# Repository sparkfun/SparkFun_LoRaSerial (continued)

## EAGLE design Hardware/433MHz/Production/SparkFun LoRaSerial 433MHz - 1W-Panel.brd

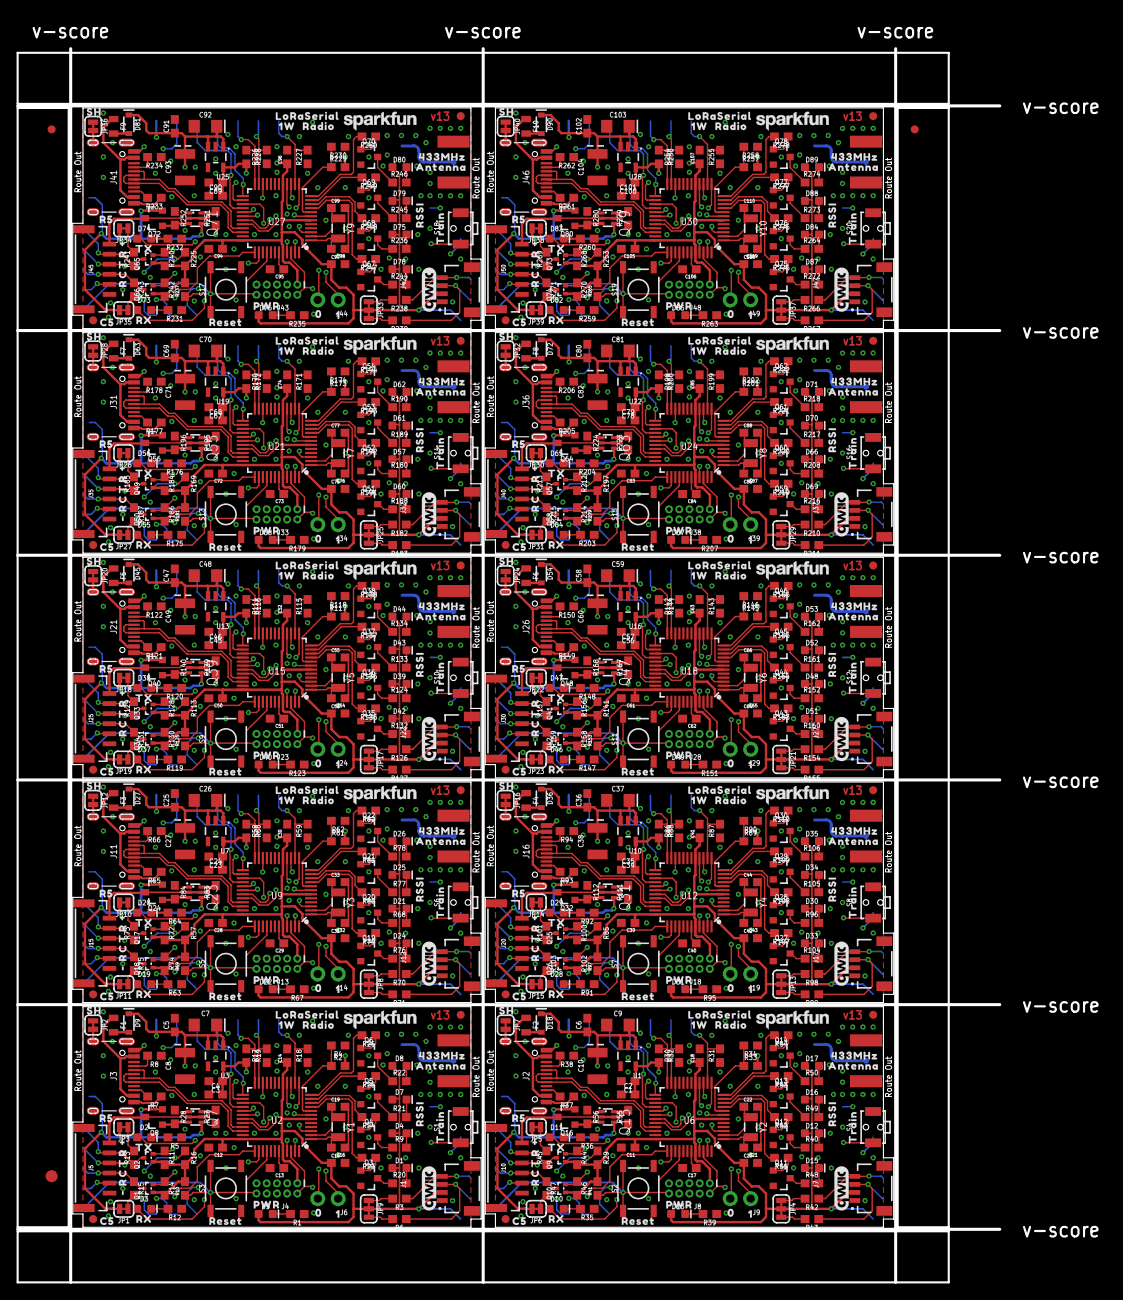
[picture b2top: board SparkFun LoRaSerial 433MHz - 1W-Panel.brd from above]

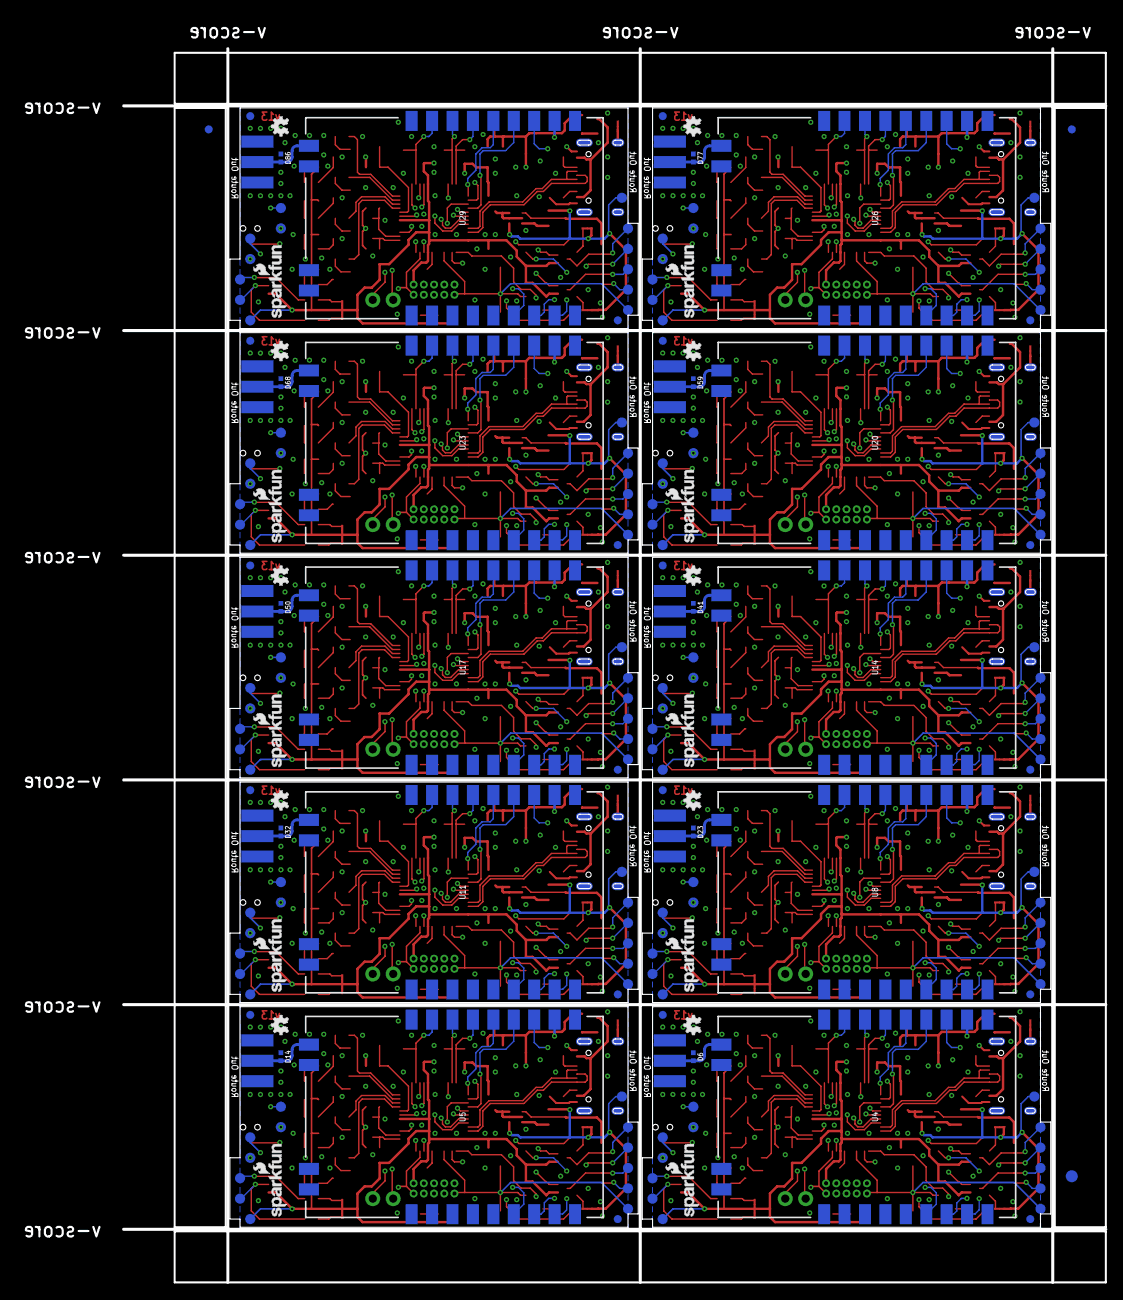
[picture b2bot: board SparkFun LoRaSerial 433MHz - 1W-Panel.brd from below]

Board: 4 copper layers, 122.2 x 153.5 mm, 1166 parts (203 on the bottom side), 660 nets.

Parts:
C1, C3, C5, C6, C23, C25, C34, C36, C45, C47, C56, C58, C67, C69, C78, C80, C89, C91, C100, C102: 1.0uF; 0603
C2, C4, C11, C12, C13, C14, C15, C17, C18, C20, C24, C28, C29, C30, C31, C35, C39, C40, C41, C42, C46, C50, C51, C52, C53, C57, C61, C62, C63, C64, C68, C72, C73, C74, C75, C79, C83, C84, C85, C86, C90, C94, C95, C96, C97, C101, C105, C106, C107, C108: 0.1uF; 0603
C7, C9, C26, C37, C48, C59, C70, C81, C92, C103: 10uF; EIA3216
C8, C10, C27, C38, C49, C60, C71, C82, C93, C104: 47uF; EIA3528
C16, C19, C21, C22, C32, C33, C43, C44, C54, C55, C65, C66, C76, C77, C87, C88, C98, C99, C109, C110: 15pF; 0603
D1, D4, D7, D8, D12, D15, D16, D17, D21, D24, D25, D26, D30, D33, D34, D35, D39, D42, D43, D44, D48, D51, D52, D53, D57, D60, D61, D62, D66, D69, D70, D71, D75, D78, D79, D80, D84, D87, D88, D89: GREEN; LED-0603
D2, D11, D20, D29, D38, D47, D56, D65, D74, D83: BLUE; LED-0603
D3, D10, D19, D28, D37, D46, D55, D64, D73, D82: Yellow; LED-0603
D5, D13, D22, D31, D40, D49, D58, D67, D76, D85: RED; LED-0603
D6, D14, D23, D32, D41, D50, D59, D68, D77, D86: PESD0402; 0402-TIGHT
D9, D18, D27, D36, D45, D54, D63, D72, D81, D90: 3A/10V/280mV; SOD-323
E1, E2, E3, E4, E5, E6, E7, E8, E9, E10: SMA; SMA-EDGE
E$1, E$2, E$3, E$4: FIDUCIAL-1X2
E$5, E$6: FIDUCIAL-1.5X3
F1, F2, F3, F4, F5, F6, F7, F8, F9, F10: 6V 0.5A; 0805
FID1, FID2, FID3, FID4, FID5, FID6, FID7, FID8, FID9, FID10, FID11, FID12, FID13, FID14, FID15, FID16, FID17, FID18, FID19, FID20, FID21, FID22, FID23, FID24, FID25, FID26, FID27, FID28, FID29, FID30, FID31, FID32, FID33, FID34, FID35, FID36, FID37, FID38, FID39, FID40: FIDUCIAL1X2; FIDUCIAL-1X2
J1, J7, J12, J17, J22, J27, J32, J37, J42, J47: QWIIC_RIGHT_ANGLE; JST04_1MM_RA
J2, J3, J11, J16, J21, J26, J31, J36, J41, J46: USB C; USB-C-16P
J4, J8, J13, J18, J23, J28, J33, J38, J43, J48: JTAG; 2X5-PTH-1.27MM-NO_SILK
J5, J10, J15, J20, J25, J30, J35, J40, J45, J50: JST-6-SMD-1.25MM-LOCKING
J6, J9, J14, J19, J24, J29, J34, J39, J44, J49: 1X02_NO_SILK
JP1, JP3, JP5, JP6, JP10, JP11, JP14, JP15, JP18, JP19, JP22, JP23, JP26, JP27, JP30, JP31, JP34, JP35, JP38, JP39: JUMPER-SMT_2_NC_TRACE_SILK; SMT-JUMPER_2_NC_TRACE_SILK
JP2, JP7, JP12, JP16, JP20, JP24, JP28, JP32, JP36, JP40: SMT-JUMPER_2_NC_TRACE_SILK
JP4, JP8, JP9, JP13, JP17, JP21, JP25, JP29, JP33, JP37: JUMPER-SMT_3_2-NC_TRACE_SILK; SMT-JUMPER_3_2-NC_TRACE_SILK
LOGO1, LOGO5, LOGO9, LOGO13, LOGO17, LOGO21, LOGO25, LOGO29, LOGO33, LOGO37: SFE_LOGO_NAME9_MM; SFE_LOGO_NAME_9MM
LOGO2, LOGO6, LOGO10, LOGO14, LOGO18, LOGO22, LOGO26, LOGO30, LOGO34, LOGO38: SFE_LOGO_NAME_FLAME9_MM; SFE_LOGO_NAME_FLAME_9MM
LOGO3, LOGO8, LOGO12, LOGO16, LOGO20, LOGO24, LOGO28, LOGO32, LOGO36, LOGO40: QWIIC_LOGO_CONNECTOR; QWIIC_5.5MM
LOGO4, LOGO7, LOGO11, LOGO15, LOGO19, LOGO23, LOGO27, LOGO31, LOGO35, LOGO39: OSHW-LOGOMINI; OSHW-LOGO-MINI
Q1, Q2, Q9, Q10, Q17, Q18, Q25, Q26, Q33, Q34, Q41, Q42, Q49, Q50, Q57, Q58, Q65, Q66, Q73, Q74: 20V/0.2A/8MHz/1.2Ω/1Vth; SOT-416FL
Q3, Q4, Q5, Q6, Q11, Q12, Q13, Q14, Q19, Q20, Q21, Q22, Q27, Q28, Q29, Q30, Q35, Q36, Q37, Q38, Q43, Q44, Q45, Q46, Q51, Q52, Q53, Q54, Q59, Q60, Q61, Q62, Q67, Q68, Q69, Q70, Q75, Q76, Q77, Q78: 600mA/40V; SOT23-3
Q7, Q15, Q23, Q31, Q39, Q47, Q55, Q63, Q71, Q79: SOT363_PHILIPS
Q8, Q16, Q24, Q32, Q40, Q48, Q56, Q64, Q72, Q80: 20V/4.2A/52mΩ/1.4W; SOT23-3
R1, R23, R24, R25, R26, R39, R51, R52, R53, R54, R67, R79, R80, R81, R82, R95, R107, R108, R109, R110, R123, R135, R136, R137, R138, R151, R163, R164, R165, R166, R179, R191, R192, R193, R194, R207, R219, R220, R221, R222, R235, R247, R248, R249, R250, R263, R275, R276, R277, R278: 1k; 0603
R2, R10, R33, R41, R61, R69, R89, R97, R117, R125, R145, R153, R173, R181, R201, R209, R229, R237, R257, R265: 10k; 0603
R3, R6, R11, R13, R14, R15, R42, R43, R44, R45, R46, R47, R70, R71, R72, R73, R74, R75, R98, R99, R100, R101, R102, R103, R126, R127, R128, R129, R130, R131, R154, R155, R156, R157, R158, R159, R182, R183, R184, R185, R186, R187, R210, R211, R212, R213, R214, R215, R238, R239, R240, R241, R242, R243, R266, R267, R268, R269, R270, R271: 2.2k; 0603
R4, R34, R62, R90, R118, R146, R174, R202, R230, R258: 20k; 0603
R5, R36, R64, R92, R120, R148, R176, R204, R232, R260: 0; 0603
R7, R8, R37, R38, R65, R66, R93, R94, R121, R122, R149, R150, R177, R178, R205, R206, R233, R234, R261, R262: 5.1k; 0603
R9, R20, R21, R22, R40, R48, R49, R50, R68, R76, R77, R78, R96, R104, R105, R106, R124, R132, R133, R134, R152, R160, R161, R162, R180, R188, R189, R190, R208, R216, R217, R218, R236, R244, R245, R246, R264, R272, R273, R274: 22Ω; 0603
R12, R35, R63, R91, R119, R147, R175, R203, R231, R259: 330; 0603
R16, R17, R18, R19, R27, R29, R30, R31, R32, R55, R57, R58, R59, R60, R83, R85, R86, R87, R88, R111, R113, R114, R115, R116, R139, R141, R142, R143, R144, R167, R169, R170, R171, R172, R195, R197, R198, R199, R200, R223, R225, R226, R227, R228, R251, R253, R254, R255, R256, R279: 100k; 0603
R28, R56, R84, R112, R140, R168, R196, R224, R252, R280: 1M; 0603
S1, S4, S6, S8, S10, S12, S14, S16, S18, S20: Train; TACTILE_SWITCH_SMD_RIGHT_ANGLE
S2, S3, S5, S7, S9, S11, S13, S15, S17, S19: Reset; TACTILE_SWITCH_SMD_5.2MM
TP1, TP2, TP3, TP4, TP5, TP6, TP7, TP8, TP9, TP10, TP11, TP12, TP13, TP14, TP15, TP16, TP17, TP18, TP19, TP20, TP21, TP22, TP23, TP24, TP25, TP26, TP27, TP28, TP29, TP30, TP31, TP32, TP33, TP34, TP35, TP36, TP37, TP38, TP39, TP40, TP41, TP42, TP43, TP44, TP45, TP46, TP47, TP48, TP49, TP50, TP51, TP52, TP53, TP54, TP55, TP56, TP57, TP58, TP59, TP60, TP61, TP62, TP63, TP64, TP65, TP66, TP67, TP68, TP69, TP70, TP71, TP72, TP73, TP74, TP75, TP76, TP77, TP78, TP79, TP80, TP81, TP82, TP83, TP84, TP85, TP86, TP87, TP88, TP89, TP90, TP91, TP92, TP93, TP94, TP95, TP96, TP97, TP98, TP99, TP100, TP101, TP102, TP103, TP104, TP105, TP106, TP107, TP108, TP109, TP110, TP111, TP112, TP113, TP114, TP115, TP116, TP117, TP118, TP119, TP120, TP121, TP122, TP123, TP124, TP125, TP126, TP127, TP128, TP129, TP130: PAD.03X.05
U1, U3, U7, U10, U13, U16, U19, U22, U25, U28: 3.3V/150mA; SOT23-5
U2, U6, U9, U12, U15, U18, U21, U24, U27, U30: ATSAMD21G-A; TQFP-48
U4, U5, U8, U11, U14, U17, U20, U23, U26, U29: E19-915M30S; E19-433M30S
U$1, U$35, U$57, U$79, U$101, U$123, U$145, U$167, U$189, U$211: 1W1
U$2, U$3, U$45, U$67, U$89, U$111, U$133, U$155, U$177, U$199: RESET0
U$4, U$36, U$58, U$80, U$102, U$124, U$146, U$168, U$190, U$212: TRAIN0
U$5, U$25, U$47, U$69, U$91, U$113, U$135, U$157, U$179, U$201: RADIO2
U$6, U$41, U$63, U$85, U$107, U$129, U$151, U$173, U$195, U$217: 01
U$7, U$40, U$62, U$84, U$106, U$128, U$150, U$172, U$194, U$216: PWR0
U$8, U$44, U$66, U$88, U$110, U$132, U$154, U$176, U$198, U$220: 433MHZ0
U$9, U$24, U$46, U$68, U$90, U$112, U$134, U$156, U$178, U$200: ANTENNA1
U$10, U$26, U$48, U$70, U$92, U$114, U$136, U$158, U$180, U$202: RX1
U$11, U$27, U$49, U$71, U$93, U$115, U$137, U$159, U$181, U$203: TX0
U$12, U$28, U$50, U$72, U$94, U$116, U$138, U$160, U$182, U$204: #0
U$13, U$29, U$51, U$73, U$95, U$117, U$139, U$161, U$183, U$205: #1
U$14, U$30, U$52, U$74, U$96, U$118, U$140, U$162, U$184, U$206: R3
U$15, U$31, U$53, U$75, U$97, U$119, U$141, U$163, U$185, U$207: T2
U$16, U$32, U$54, U$76, U$98, U$120, U$142, U$164, U$186, U$208: C0
U$17, U$33, U$55, U$77, U$99, U$121, U$143, U$165, U$187, U$209: R1
U$18, U$34, U$56, U$78, U$100, U$122, U$144, U$166, U$188, U$210: LORASERIAL0
U$19, U$37, U$59, U$81, U$103, U$125, U$147, U$169, U$191, U$213: C50
U$20, U$38, U$60, U$82, U$104, U$126, U$148, U$170, U$192, U$214: R50
U$21, U$39, U$61, U$83, U$105, U$127, U$149, U$171, U$193, U$215: RSSI0
U$22, U$42, U$64, U$86, U$108, U$130, U$152, U$174, U$196, U$218: 10
U$23, U$43, U$65, U$87, U$109, U$131, U$153, U$175, U$197, U$219: SH0
Y1, Y2, Y3, Y4, Y5, Y6, Y7, Y8, Y9, Y10: 32.768kHz; CRYSTAL-SMD-3.2X1.5MM

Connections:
3.3V: C3.1, C4.2, C12.1, C14.1, C15.1, D1.A, D4.A, D5.A, D7.A, D8.A, J1.2, J4.1, JP9.2, Q1.1, Q2.1, R2.2, R10.2, R11.2, R14.2, R16.2, R17.2, TP1.1, U2.6, U2.17, U2.36, U2.44, U3.5
3.3V1: C1.1, C2.2, C11.1, C18.1, C20.1, D12.A, D13.A, D15.A, D16.A, D17.A, J7.2, J8.1, JP4.2, Q9.1, Q10.1, R29.2, R30.2, R33.2, R41.2, R44.2, R46.2, TP14.1, U1.5, U6.6, U6.17, U6.36, U6.44
3.3V2: C23.1, C24.2, C28.1, C30.1, C31.1, D21.A, D22.A, D24.A, D25.A, D26.A, J12.2, J13.1, JP8.2, Q17.1, Q18.1, R57.2, R58.2, R61.2, R69.2, R72.2, R74.2, TP27.1, U7.5, U9.6, U9.17, U9.36, U9.44
3.3V3: C34.1, C35.2, C39.1, C41.1, C42.1, D30.A, D31.A, D33.A, D34.A, D35.A, J17.2, J18.1, JP13.2, Q25.1, Q26.1, R85.2, R86.2, R89.2, R97.2, R100.2, R102.2, TP40.1, U10.5, U12.6, U12.17, U12.36, U12.44
3.3V4: C45.1, C46.2, C50.1, C52.1, C53.1, D39.A, D40.A, D42.A, D43.A, D44.A, J22.2, J23.1, JP17.2, Q33.1, Q34.1, R113.2, R114.2, R117.2, R125.2, R128.2, R130.2, TP53.1, U13.5, U15.6, U15.17, U15.36, U15.44
3.3V5: C56.1, C57.2, C61.1, C63.1, C64.1, D48.A, D49.A, D51.A, D52.A, D53.A, J27.2, J28.1, JP21.2, Q41.1, Q42.1, R141.2, R142.2, R145.2, R153.2, R156.2, R158.2, TP66.1, U16.5, U18.6, U18.17, U18.36, U18.44
3.3V6: C67.1, C68.2, C72.1, C74.1, C75.1, D57.A, D58.A, D60.A, D61.A, D62.A, J32.2, J33.1, JP25.2, Q49.1, Q50.1, R169.2, R170.2, R173.2, R181.2, R184.2, R186.2, TP79.1, U19.5, U21.6, U21.17, U21.36, U21.44
3.3V7: C78.1, C79.2, C83.1, C85.1, C86.1, D66.A, D67.A, D69.A, D70.A, D71.A, J37.2, J38.1, JP29.2, Q57.1, Q58.1, R197.2, R198.2, R201.2, R209.2, R212.2, R214.2, TP92.1, U22.5, U24.6, U24.17, U24.36, U24.44
3.3V8: C89.1, C90.2, C94.1, C96.1, C97.1, D75.A, D76.A, D78.A, D79.A, D80.A, J42.2, J43.1, JP33.2, Q65.1, Q66.1, R225.2, R226.2, R229.2, R237.2, R240.2, R242.2, TP105.1, U25.5, U27.6, U27.17, U27.36, U27.44
3.3V9: C100.1, C101.2, C105.1, C107.1, C108.1, D84.A, D85.A, D87.A, D88.A, D89.A, J47.2, J48.1, JP37.2, Q73.1, Q74.1, R253.2, R254.2, R257.2, R265.2, R268.2, R270.2, TP118.1, U28.5, U30.6, U30.17, U30.36, U30.44
5V: C5.1, C7.+, C8.A, D9.C, JP1.2, JP3.2, Q7.4, Q8.2, TP2.1, U3.1, U3.3, U4.11
5V1: C6.1, C9.+, C10.A, D18.C, JP5.2, JP6.2, Q15.4, Q16.2, TP15.1, U1.1, U1.3, U5.11
5V2: C25.1, C26.+, C27.A, D27.C, JP10.2, JP11.2, Q23.4, Q24.2, TP28.1, U7.1, U7.3, U8.11
5V3: C36.1, C37.+, C38.A, D36.C, JP14.2, JP15.2, Q31.4, Q32.2, TP41.1, U10.1, U10.3, U11.11
5V4: C47.1, C48.+, C49.A, D45.C, JP18.2, JP19.2, Q39.4, Q40.2, TP54.1, U13.1, U13.3, U14.11
5V5: C58.1, C59.+, C60.A, D54.C, JP22.2, JP23.2, Q47.4, Q48.2, TP67.1, U16.1, U16.3, U17.11
5V6: C69.1, C70.+, C71.A, D63.C, JP26.2, JP27.2, Q55.4, Q56.2, TP80.1, U19.1, U19.3, U20.11
5V7: C80.1, C81.+, C82.A, D72.C, JP30.2, JP31.2, Q63.4, Q64.2, TP93.1, U22.1, U22.3, U23.11
5V8: C91.1, C92.+, C93.A, D81.C, JP34.2, JP35.2, Q71.4, Q72.2, TP106.1, U25.1, U25.3, U26.11
5V9: C102.1, C103.+, C104.A, D90.C, JP38.2, JP39.2, Q79.4, Q80.2, TP119.1, U28.1, U28.3, U29.11
A0: J6.2, TP12.1, U2.3
A1: J6.1, TP13.1, U2.7
A2: J9.1, TP26.1, U6.7
A2/BOARD_ID: R2.1, R4.2, U2.8
A2/BOARD_ID1: R33.1, R34.2, U6.8
A2/BOARD_ID2: R61.1, R62.2, U9.8
A2/BOARD_ID3: R89.1, R90.2, U12.8
A2/BOARD_ID4: R117.1, R118.2, U15.8
A2/BOARD_ID5: R145.1, R146.2, U18.8
A2/BOARD_ID6: R173.1, R174.2, U21.8
A2/BOARD_ID7: R201.1, R202.2, U24.8
A2/BOARD_ID8: R229.1, R230.2, U27.8
A2/BOARD_ID9: R257.1, R258.2, U30.8
A3: J9.2, TP25.1, U6.3
A3/RSSI1: R23.2, U2.9
A3/RSSI2: R51.2, U6.9
A3/RSSI3: R79.2, U9.9
A3/RSSI4: R107.2, U12.9
A3/RSSI5: R135.2, U15.9
A3/RSSI6: R163.2, U18.9
A3/RSSI7: R191.2, U21.9
A3/RSSI8: R219.2, U24.9
A3/RSSI9: R247.2, U27.9
A3/RSSI10: R275.2, U30.9
A4: J14.1, TP39.1, U9.7
A4/RSSI1: R52.2, U6.10
A4/RSSI2: R24.2, U2.10
A4/RSSI3: R80.2, U9.10
A4/RSSI4: R108.2, U12.10
A4/RSSI5: R136.2, U15.10
A4/RSSI6: R164.2, U18.10
A4/RSSI7: R192.2, U21.10
A4/RSSI8: R220.2, U24.10
A4/RSSI9: R248.2, U27.10
A4/RSSI10: R276.2, U30.10
A5: J14.2, TP38.1, U9.3
A5/RX_LED: D3.A, U2.47
A5/RX_LED1: D10.A, U6.47
A5/RX_LED2: D19.A, U9.47
A5/RX_LED3: D28.A, U12.47
A5/RX_LED4: D37.A, U15.47
A5/RX_LED5: D46.A, U18.47
A5/RX_LED6: D55.A, U21.47
A5/RX_LED7: D64.A, U24.47
A5/RX_LED8: D73.A, U27.47
A5/RX_LED9: D82.A, U30.47
A6: J19.1, TP52.1, U12.7
A7: J19.2, TP51.1, U12.3
A8: J24.1, TP65.1, U15.7
A9: J24.2, TP64.1, U15.3
A10: J29.1, TP78.1, U18.7
A11: J29.2, TP77.1, U18.3
A12: J34.1, TP91.1, U21.7
A13: J34.2, TP90.1, U21.3
A14: J39.1, TP104.1, U24.7
A15: J39.2, TP103.1, U24.3
A16: J44.1, TP117.1, U27.7
A17: J44.2, TP116.1, U27.3
A18: J49.1, TP130.1, U30.7
A19: J49.2, TP129.1, U30.3
CC1: J3.A5, R8.2
CC2: J3.B5, R7.2
CC3: J2.B5, R37.2
CC4: J2.A5, R38.2
CC5: J11.B5, R65.2
CC6: J11.A5, R66.2
CC7: J16.B5, R93.2
CC8: J16.A5, R94.2
CC9: J21.B5, R121.2
CC10: J21.A5, R122.2
CC11: J26.B5, R149.2
CC12: J26.A5, R150.2
CC13: J31.B5, R177.2
CC14: J31.A5, R178.2
CC15: J36.B5, R205.2
CC16: J36.A5, R206.2
CC17: J41.B5, R233.2
CC18: J41.A5, R234.2
CC19: J46.B5, R261.2
CC20: J46.A5, R262.2
CTS-I_HV: J5.4, Q1.3, R15.1, TP6.1
CTS-I_HV1: J10.4, Q10.3, R47.1, TP19.1
CTS-I_HV2: J15.4, Q18.3, R75.1, TP32.1
CTS-I_HV3: J20.4, Q26.3, R103.1, TP45.1
CTS-I_HV4: J25.4, Q34.3, R131.1, TP58.1
CTS-I_HV5: J30.4, Q42.3, R159.1, TP71.1
CTS-I_HV6: J35.4, Q50.3, R187.1, TP84.1
CTS-I_HV7: J40.4, Q58.3, R215.1, TP97.1
CTS-I_HV8: J45.4, Q66.3, R243.1, TP110.1
CTS-I_HV9: J50.4, Q74.3, R271.1, TP123.1
D2/LORA_TXEN: R19.2, U2.23, U4.16
D2/LORA_TXEN1: R32.2, U5.16, U6.23
D2/LORA_TXEN2: R60.2, U8.16, U9.23
D2/LORA_TXEN3: R88.2, U11.16, U12.23
D2/LORA_TXEN4: R116.2, U14.16, U15.23
D2/LORA_TXEN5: R144.2, U17.16, U18.23
D2/LORA_TXEN6: R172.2, U20.16, U21.23
D2/LORA_TXEN7: R200.2, U23.16, U24.23
D2/LORA_TXEN8: R228.2, U26.16, U27.23
D2/LORA_TXEN9: R256.2, U29.16, U30.23
D3/LORA_RXEN: R18.2, U2.14, U4.17
D3/LORA_RXEN1: R31.2, U5.17, U6.14
D3/LORA_RXEN2: R59.2, U8.17, U9.14
D3/LORA_RXEN3: R87.2, U11.17, U12.14
D3/LORA_RXEN4: R115.2, U14.17, U15.14
D3/LORA_RXEN5: R143.2, U17.17, U18.14
D3/LORA_RXEN6: R171.2, U20.17, U21.14
D3/LORA_RXEN7: R199.2, U23.17, U24.14
D3/LORA_RXEN8: R227.2, U26.17, U27.14
D3/LORA_RXEN9: R255.2, U29.17, U30.14
D4/TRAIN: S1.1, U2.13
D4/TRAIN1: S4.1, U6.13
D4/TRAIN2: S6.1, U9.13
D4/TRAIN3: S8.1, U12.13
D4/TRAIN4: S10.1, U15.13
D4/TRAIN5: S12.1, U18.13
D4/TRAIN6: S14.1, U21.13
D4/TRAIN7: S16.1, U24.13
D4/TRAIN8: S18.1, U27.13
D4/TRAIN9: S20.1, U30.13
D5/LORA_!CS!: R17.1, U2.24, U4.15
D5/LORA_!CS!1: R30.1, U5.15, U6.24
D5/LORA_!CS!2: R58.1, U8.15, U9.24
D5/LORA_!CS!3: R86.1, U11.15, U12.24
D5/LORA_!CS!4: R114.1, U14.15, U15.24
D5/LORA_!CS!5: R142.1, U17.15, U18.24
D5/LORA_!CS!6: R170.1, U20.15, U21.24
D5/LORA_!CS!7: R198.1, U23.15, U24.24
D5/LORA_!CS!8: R226.1, U26.15, U27.24
D5/LORA_!CS!9: R254.1, U29.15, U30.24
D6/LORA_!RST!: R16.1, U2.29, U4.8
D6/LORA_!RST!1: R29.1, U5.8, U6.29
D6/LORA_!RST!2: R57.1, U8.8, U9.29
D6/LORA_!RST!3: R85.1, U11.8, U12.29
D6/LORA_!RST!4: R113.1, U14.8, U15.29
D6/LORA_!RST!5: R141.1, U17.8, U18.29
D6/LORA_!RST!6: R169.1, U20.8, U21.29
D6/LORA_!RST!7: R197.1, U23.8, U24.29
D6/LORA_!RST!8: R225.1, U26.8, U27.29
D6/LORA_!RST!9: R253.1, U29.8, U30.29
D7/LORA_D0: U2.30, U4.7
D7/LORA_D1: U5.7, U6.30
D7/LORA_D2: U8.7, U9.30
D7/LORA_D3: U11.7, U12.30
D7/LORA_D4: U14.7, U15.30
D7/LORA_D5: U17.7, U18.30
D7/LORA_D6: U20.7, U21.30
D7/LORA_D7: U23.7, U24.30
D7/LORA_D8: U26.7, U27.30
D7/LORA_D9: U29.7, U30.30
D8/RSSI1: R53.2, U6.11
D8/RSSI2: R81.2, U9.11
D8/RSSI3: R25.2, U2.11
D8/RSSI4: R109.2, U12.11
D8/RSSI5: R137.2, U15.11
D8/RSSI6: R165.2, U18.11
D8/RSSI7: R193.2, U21.11
D8/RSSI8: R221.2, U24.11
D8/RSSI9: R249.2, U27.11
D8/RSSI10: R277.2, U30.11
D9/RSSI1: R54.2, U6.12
D9/RSSI2: R82.2, U9.12
D9/RSSI3: R110.2, U12.12
D9/RSSI4: R26.2, U2.12
D9/RSSI5: R138.2, U15.12
D9/RSSI6: R166.2, U18.12
D9/RSSI7: R194.2, U21.12
D9/RSSI8: R222.2, U24.12
D9/RSSI9: R250.2, U27.12
D9/RSSI10: R278.2, U30.12
D10/LORA_D1: U2.27, U4.6
D10/LORA_D2: U5.6, U6.27
D10/LORA_D3: U8.6, U9.27
D10/LORA_D4: U11.6, U12.27
D10/LORA_D5: U14.6, U15.27
D10/LORA_D6: U17.6, U18.27
D10/LORA_D7: U20.6, U21.27
D10/LORA_D8: U23.6, U24.27
D10/LORA_D9: U26.6, U27.27
D10/LORA_D10: U29.6, U30.27
D11/SPI_PICO: U2.25, U4.14
D11/SPI_PICO1: U5.14, U6.25
D11/SPI_PICO2: U8.14, U9.25
D11/SPI_PICO3: U11.14, U12.25
D11/SPI_PICO4: U14.14, U15.25
D11/SPI_PICO5: U17.14, U18.25
D11/SPI_PICO6: U20.14, U21.25
D11/SPI_PICO7: U23.14, U24.25
D11/SPI_PICO8: U26.14, U27.25
D11/SPI_PICO9: U29.14, U30.25
D12/SPI_POCI: U2.28, U4.13
D12/SPI_POCI1: U5.13, U6.28
D12/SPI_POCI2: U8.13, U9.28
D12/SPI_POCI3: U11.13, U12.28
D12/SPI_POCI4: U14.13, U15.28
D12/SPI_POCI5: U17.13, U18.28
D12/SPI_POCI6: U20.13, U21.28
D12/SPI_POCI7: U23.13, U24.28
D12/SPI_POCI8: U26.13, U27.28
D12/SPI_POCI9: U29.13, U30.28
D13/SPI_SCK: U2.26, U4.12
D13/SPI_SCK1: U5.12, U6.26
D13/SPI_SCK2: U8.12, U9.26
D13/SPI_SCK3: U11.12, U12.26
D13/SPI_SCK4: U14.12, U15.26
D13/SPI_SCK5: U17.12, U18.26
D13/SPI_SCK6: U20.12, U21.26
D13/SPI_SCK7: U23.12, U24.26
D13/SPI_SCK8: U26.12, U27.26
D13/SPI_SCK9: U29.12, U30.26
D20/SDA: J1.3, R6.1, TP10.1, U2.31
D20/SDA1: J7.3, R43.1, TP23.1, U6.31
D20/SDA2: J12.3, R71.1, TP36.1, U9.31
D20/SDA3: J17.3, R99.1, TP49.1, U12.31
D20/SDA4: J22.3, R127.1, TP62.1, U15.31
D20/SDA5: J27.3, R155.1, TP75.1, U18.31
D20/SDA6: J32.3, R183.1, TP88.1, U21.31
D20/SDA7: J37.3, R211.1, TP101.1, U24.31
D20/SDA8: J42.3, R239.1, TP114.1, U27.31
D20/SDA9: J47.3, R267.1, TP127.1, U30.31
D21/SCL: J1.4, R3.1, TP11.1, U2.32
D21/SCL1: J7.4, R42.1, TP24.1, U6.32
D21/SCL2: J12.4, R70.1, TP37.1, U9.32
D21/SCL3: J17.4, R98.1, TP50.1, U12.32
D21/SCL4: J22.4, R126.1, TP63.1, U15.32
D21/SCL5: J27.4, R154.1, TP76.1, U18.32
D21/SCL6: J32.4, R182.1, TP89.1, U21.32
D21/SCL7: J37.4, R210.1, TP102.1, U24.32
D21/SCL8: J42.4, R238.1, TP115.1, U27.32
D21/SCL9: J47.4, R266.1, TP128.1, U30.32
D28/USB_D-: J3.A7, J3.B7, U2.33
D28/USB_D-1: J2.A7, J2.B7, U6.33
D28/USB_D-2: J11.A7, J11.B7, U9.33
D28/USB_D-3: J16.A7, J16.B7, U12.33
D28/USB_D-4: J21.A7, J21.B7, U15.33
D28/USB_D-5: J26.A7, J26.B7, U18.33
D28/USB_D-6: J31.A7, J31.B7, U21.33
D28/USB_D-7: J36.A7, J36.B7, U24.33
D28/USB_D-8: J41.A7, J41.B7, U27.33
D28/USB_D-9: J46.A7, J46.B7, U30.33
D29/USB_D+: J3.A6, J3.B6, U2.34
D29/USB_D+1: J2.A6, J2.B6, U6.34
D29/USB_D+2: J11.A6, J11.B6, U9.34
D29/USB_D+3: J16.A6, J16.B6, U12.34
D29/USB_D+4: J21.A6, J21.B6, U15.34
D29/USB_D+5: J26.A6, J26.B6, U18.34
D29/USB_D+6: J31.A6, J31.B6, U21.34
D29/USB_D+7: J36.A6, J36.B6, U24.34
D29/USB_D+8: J41.A6, J41.B6, U27.34
D29/USB_D+9: J46.A6, J46.B6, U30.34
D30/CTS-I_LV: Q1.2, R14.1, U2.37
D30/CTS-I_LV1: Q10.2, R46.1, U6.37
D30/CTS-I_LV2: Q18.2, R74.1, U9.37
D30/CTS-I_LV3: Q26.2, R102.1, U12.37
D30/CTS-I_LV4: Q34.2, R130.1, U15.37
D30/CTS-I_LV5: Q42.2, R158.1, U18.37
D30/CTS-I_LV6: Q50.2, R186.1, U21.37
D30/CTS-I_LV7: Q58.2, R214.1, U24.37
D30/CTS-I_LV8: Q66.2, R242.1, U27.37
D30/CTS-I_LV9: Q74.2, R270.1, U30.37
D31/TX_LED: D2.A, U2.38
D31/TX_LED1: D11.A, U6.38
D31/TX_LED2: D20.A, U9.38
D31/TX_LED3: D29.A, U12.38
D31/TX_LED4: D38.A, U15.38
D31/TX_LED5: D47.A, U18.38
D31/TX_LED6: D56.A, U21.38
D31/TX_LED7: D65.A, U24.38
D31/TX_LED8: D74.A, U27.38
D31/TX_LED9: D83.A, U30.38
D38/RTS-O: J5.5, TP9.1, U2.22
D38/RTS-O1: J10.5, TP22.1, U6.22
D38/RTS-O2: J15.5, TP35.1, U9.22
D38/RTS-O3: J20.5, TP48.1, U12.22
D38/RTS-O4: J25.5, TP61.1, U15.22
D38/RTS-O5: J30.5, TP74.1, U18.22
D38/RTS-O6: J35.5, TP87.1, U21.22
D38/RTS-O7: J40.5, TP100.1, U24.22
D38/RTS-O8: J45.5, TP113.1, U27.22
D38/RTS-O9: J50.5, TP126.1, U30.22
GND: C3.2, C4.1, C5.2, C7.-, C8.C, C12.2, C13.2, C14.2, C15.2, C16.1, C19.2, D6.1, E2.GND@0, E2.GND@1, E2.GND@2, E2.GND@3, J1.1, J3.GND, J3.GND2, J4.3, J4.5, J4.9, J5.6, JP2.1, Q3.2, Q4.2, Q5.2, Q6.2, R1.1, R4.1, R5.1, R7.1, R8.1, R12.1, R18.1, R19.1, R27.1, R28.1, S1.2, S3.3, S3.4, U2.5, U2.18, U2.35, U2.42, U3.2, U4.1, U4.9, U4.10, U4.18, U4.20, U4.21, U4.22
GND1: C1.2, C2.1, C6.2, C9.-, C10.C, C11.2, C17.2, C18.2, C20.2, C21.1, C22.2, D14.1, E1.GND@0, E1.GND@1, E1.GND@2, E1.GND@3, J2.GND, J2.GND2, J7.1, J8.3, J8.5, J8.9, J10.6, JP7.1, Q11.2, Q12.2, Q13.2, Q14.2, R31.1, R32.1, R34.1, R35.1, R36.1, R37.1, R38.1, R39.1, R55.1, R56.1, S2.3, S2.4, S4.2, U1.2, U5.1, U5.9, U5.10, U5.18, U5.20, U5.21, U5.22, U6.5, U6.18, U6.35, U6.42
GND2: C23.2, C24.1, C25.2, C26.-, C27.C, C28.2, C29.2, C30.2, C31.2, C32.1, C33.2, D23.1, E3.GND@0, E3.GND@1, E3.GND@2, E3.GND@3, J11.GND, J11.GND2, J12.1, J13.3, J13.5, J13.9, J15.6, JP12.1, Q19.2, Q20.2, Q21.2, Q22.2, R59.1, R60.1, R62.1, R63.1, R64.1, R65.1, R66.1, R67.1, R83.1, R84.1, S5.3, S5.4, S6.2, U7.2, U8.1, U8.9, U8.10, U8.18, U8.20, U8.21, U8.22, U9.5, U9.18, U9.35, U9.42
GND3: C34.2, C35.1, C36.2, C37.-, C38.C, C39.2, C40.2, C41.2, C42.2, C43.1, C44.2, D32.1, E4.GND@0, E4.GND@1, E4.GND@2, E4.GND@3, J16.GND, J16.GND2, J17.1, J18.3, J18.5, J18.9, J20.6, JP16.1, Q27.2, Q28.2, Q29.2, Q30.2, R87.1, R88.1, R90.1, R91.1, R92.1, R93.1, R94.1, R95.1, R111.1, R112.1, S7.3, S7.4, S8.2, U10.2, U11.1, U11.9, U11.10, U11.18, U11.20, U11.21, U11.22, U12.5, U12.18, U12.35, U12.42
GND4: C45.2, C46.1, C47.2, C48.-, C49.C, C50.2, C51.2, C52.2, C53.2, C54.1, C55.2, D41.1, E5.GND@0, E5.GND@1, E5.GND@2, E5.GND@3, J21.GND, J21.GND2, J22.1, J23.3, J23.5, J23.9, J25.6, JP20.1, Q35.2, Q36.2, Q37.2, Q38.2, R115.1, R116.1, R118.1, R119.1, R120.1, R121.1, R122.1, R123.1, R139.1, R140.1, S9.3, S9.4, S10.2, U13.2, U14.1, U14.9, U14.10, U14.18, U14.20, U14.21, U14.22, U15.5, U15.18, U15.35, U15.42
GND5: C56.2, C57.1, C58.2, C59.-, C60.C, C61.2, C62.2, C63.2, C64.2, C65.1, C66.2, D50.1, E6.GND@0, E6.GND@1, E6.GND@2, E6.GND@3, J26.GND, J26.GND2, J27.1, J28.3, J28.5, J28.9, J30.6, JP24.1, Q43.2, Q44.2, Q45.2, Q46.2, R143.1, R144.1, R146.1, R147.1, R148.1, R149.1, R150.1, R151.1, R167.1, R168.1, S11.3, S11.4, S12.2, U16.2, U17.1, U17.9, U17.10, U17.18, U17.20, U17.21, U17.22, U18.5, U18.18, U18.35, U18.42
GND6: C67.2, C68.1, C69.2, C70.-, C71.C, C72.2, C73.2, C74.2, C75.2, C76.1, C77.2, D59.1, E7.GND@0, E7.GND@1, E7.GND@2, E7.GND@3, J31.GND, J31.GND2, J32.1, J33.3, J33.5, J33.9, J35.6, JP28.1, Q51.2, Q52.2, Q53.2, Q54.2, R171.1, R172.1, R174.1, R175.1, R176.1, R177.1, R178.1, R179.1, R195.1, R196.1, S13.3, S13.4, S14.2, U19.2, U20.1, U20.9, U20.10, U20.18, U20.20, U20.21, U20.22, U21.5, U21.18, U21.35, U21.42
GND7: C78.2, C79.1, C80.2, C81.-, C82.C, C83.2, C84.2, C85.2, C86.2, C87.1, C88.2, D68.1, E8.GND@0, E8.GND@1, E8.GND@2, E8.GND@3, J36.GND, J36.GND2, J37.1, J38.3, J38.5, J38.9, J40.6, JP32.1, Q59.2, Q60.2, Q61.2, Q62.2, R199.1, R200.1, R202.1, R203.1, R204.1, R205.1, R206.1, R207.1, R223.1, R224.1, S15.3, S15.4, S16.2, U22.2, U23.1, U23.9, U23.10, U23.18, U23.20, U23.21, U23.22, U24.5, U24.18, U24.35, U24.42
GND8: C89.2, C90.1, C91.2, C92.-, C93.C, C94.2, C95.2, C96.2, C97.2, C98.1, C99.2, D77.1, E9.GND@0, E9.GND@1, E9.GND@2, E9.GND@3, J41.GND, J41.GND2, J42.1, J43.3, J43.5, J43.9, J45.6, JP36.1, Q67.2, Q68.2, Q69.2, Q70.2, R227.1, R228.1, R230.1, R231.1, R232.1, R233.1, R234.1, R235.1, R251.1, R252.1, S17.3, S17.4, S18.2, U25.2, U26.1, U26.9, U26.10, U26.18, U26.20, U26.21, U26.22, U27.5, U27.18, U27.35, U27.42
GND9: C100.2, C101.1, C102.2, C103.-, C104.C, C105.2, C106.2, C107.2, C108.2, C109.1, C110.2, D86.1, E10.GND@0, E10.GND@1, E10.GND@2, E10.GND@3, J46.GND, J46.GND2, J47.1, J48.3, J48.5, J48.9, J50.6, JP40.1, Q75.2, Q76.2, Q77.2, Q78.2, R255.1, R256.1, R258.1, R259.1, R260.1, R261.1, R262.1, R263.1, R279.1, R280.1, S19.3, S19.4, S20.2, U28.2, U29.1, U29.9, U29.10, U29.18, U29.20, U29.21, U29.22, U30.5, U30.18, U30.35, U30.42
LORA_ANT: D6.2, E2.SIG, U4.19
LORA_ANT1: D14.2, E1.SIG, U5.19
LORA_ANT2: D23.2, E3.SIG, U8.19
LORA_ANT3: D32.2, E4.SIG, U11.19
LORA_ANT4: D41.2, E5.SIG, U14.19
LORA_ANT5: D50.2, E6.SIG, U17.19
LORA_ANT6: D59.2, E7.SIG, U20.19
LORA_ANT7: D68.2, E8.SIG, U23.19
LORA_ANT8: D77.2, E9.SIG, U26.19
LORA_ANT9: D86.2, E10.SIG, U29.19
unnamed: C19.1, U2.2, Y1.P$1
unnamed: C16.2, U2.1, Y1.P$2
unnamed: D3.C, R12.2
unnamed: D2.C, R5.2
unnamed: JP3.1, R13.2
unnamed: JP1.1, R15.2
unnamed: D5.C, R1.2
unnamed: D4.C, R9.2
unnamed: D1.C, R20.2
unnamed: D7.C, R21.2
unnamed: D8.C, R22.2
unnamed: Q3.3, R20.1
unnamed: Q3.1, R23.1
unnamed: Q4.3, R9.1
unnamed: Q4.1, R24.1
unnamed: Q5.3, R21.1
unnamed: Q5.1, R25.1
unnamed: Q6.3, R22.1
unnamed: Q6.1, R26.1
unnamed: J3.SHLD1, J3.SHLD2, J3.SHLD3, J3.SHLD4, J3.SHLD5, J3.SHLD6, J3.SHLD7, J3.SHLD8, JP2.2
unnamed: Q7.3, Q8.1, R28.2
unnamed: Q7.2, Q7.5, Q7.6, R27.2
unnamed: D13.C, R39.2
unnamed: D12.C, R40.2
unnamed: C21.2, U6.1, Y2.P$2
unnamed: C22.1, U6.2, Y2.P$1
unnamed: D10.C, R35.2
unnamed: D11.C, R36.2
unnamed: JP5.1, R45.2
unnamed: JP6.1, R47.2
unnamed: D15.C, R48.2
unnamed: D16.C, R49.2
unnamed: D17.C, R50.2
unnamed: Q11.3, R48.1
unnamed: Q11.1, R51.1
unnamed: Q12.3, R40.1
unnamed: Q12.1, R52.1
unnamed: Q13.3, R49.1
unnamed: Q13.1, R53.1
unnamed: Q14.3, R50.1
unnamed: Q14.1, R54.1
unnamed: J2.SHLD1, J2.SHLD2, J2.SHLD3, J2.SHLD4, J2.SHLD5, J2.SHLD6, J2.SHLD7, J2.SHLD8, JP7.2
unnamed: Q15.3, Q16.1, R56.2
unnamed: Q15.2, Q15.5, Q15.6, R55.2
unnamed: D22.C, R67.2
unnamed: D21.C, R68.2
unnamed: C32.2, U9.1, Y3.P$2
unnamed: C33.1, U9.2, Y3.P$1
unnamed: D19.C, R63.2
unnamed: D20.C, R64.2
unnamed: JP10.1, R73.2
unnamed: JP11.1, R75.2
unnamed: D24.C, R76.2
unnamed: D25.C, R77.2
unnamed: D26.C, R78.2
unnamed: Q19.3, R76.1
unnamed: Q19.1, R79.1
unnamed: Q20.3, R68.1
unnamed: Q20.1, R80.1
unnamed: Q21.3, R77.1
unnamed: Q21.1, R81.1
unnamed: Q22.3, R78.1
unnamed: Q22.1, R82.1
unnamed: J11.SHLD1, J11.SHLD2, J11.SHLD3, J11.SHLD4, J11.SHLD5, J11.SHLD6, J11.SHLD7, J11.SHLD8, JP12.2
unnamed: Q23.3, Q24.1, R84.2
unnamed: Q23.2, Q23.5, Q23.6, R83.2
unnamed: D31.C, R95.2
unnamed: D30.C, R96.2
unnamed: C43.2, U12.1, Y4.P$2
unnamed: C44.1, U12.2, Y4.P$1
unnamed: D28.C, R91.2
unnamed: D29.C, R92.2
unnamed: JP14.1, R101.2
unnamed: JP15.1, R103.2
unnamed: D33.C, R104.2
unnamed: D34.C, R105.2
unnamed: D35.C, R106.2
unnamed: Q27.3, R104.1
unnamed: Q27.1, R107.1
unnamed: Q28.3, R96.1
unnamed: Q28.1, R108.1
unnamed: Q29.3, R105.1
unnamed: Q29.1, R109.1
unnamed: Q30.3, R106.1
unnamed: Q30.1, R110.1
unnamed: J16.SHLD1, J16.SHLD2, J16.SHLD3, J16.SHLD4, J16.SHLD5, J16.SHLD6, J16.SHLD7, J16.SHLD8, JP16.2
unnamed: Q31.3, Q32.1, R112.2
unnamed: Q31.2, Q31.5, Q31.6, R111.2
unnamed: D40.C, R123.2
unnamed: D39.C, R124.2
unnamed: C54.2, U15.1, Y5.P$2
unnamed: C55.1, U15.2, Y5.P$1
unnamed: D37.C, R119.2
unnamed: D38.C, R120.2
unnamed: JP18.1, R129.2
unnamed: JP19.1, R131.2
unnamed: D42.C, R132.2
unnamed: D43.C, R133.2
unnamed: D44.C, R134.2
unnamed: Q35.3, R132.1
unnamed: Q35.1, R135.1
unnamed: Q36.3, R124.1
unnamed: Q36.1, R136.1
unnamed: Q37.3, R133.1
unnamed: Q37.1, R137.1
unnamed: Q38.3, R134.1
unnamed: Q38.1, R138.1
unnamed: J21.SHLD1, J21.SHLD2, J21.SHLD3, J21.SHLD4, J21.SHLD5, J21.SHLD6, J21.SHLD7, J21.SHLD8, JP20.2
unnamed: Q39.3, Q40.1, R140.2
unnamed: Q39.2, Q39.5, Q39.6, R139.2
unnamed: D49.C, R151.2
unnamed: D48.C, R152.2
unnamed: C65.2, U18.1, Y6.P$2
unnamed: C66.1, U18.2, Y6.P$1
unnamed: D46.C, R147.2
unnamed: D47.C, R148.2
unnamed: JP22.1, R157.2
unnamed: JP23.1, R159.2
unnamed: D51.C, R160.2
unnamed: D52.C, R161.2
unnamed: D53.C, R162.2
unnamed: Q43.3, R160.1
unnamed: Q43.1, R163.1
unnamed: Q44.3, R152.1
unnamed: Q44.1, R164.1
unnamed: Q45.3, R161.1
unnamed: Q45.1, R165.1
unnamed: Q46.3, R162.1
unnamed: Q46.1, R166.1
unnamed: J26.SHLD1, J26.SHLD2, J26.SHLD3, J26.SHLD4, J26.SHLD5, J26.SHLD6, J26.SHLD7, J26.SHLD8, JP24.2
unnamed: Q47.3, Q48.1, R168.2
unnamed: Q47.2, Q47.5, Q47.6, R167.2
unnamed: D58.C, R179.2
unnamed: D57.C, R180.2
unnamed: C76.2, U21.1, Y7.P$2
unnamed: C77.1, U21.2, Y7.P$1
unnamed: D55.C, R175.2
unnamed: D56.C, R176.2
unnamed: JP26.1, R185.2
unnamed: JP27.1, R187.2
unnamed: D60.C, R188.2
unnamed: D61.C, R189.2
unnamed: D62.C, R190.2
unnamed: Q51.3, R188.1
unnamed: Q51.1, R191.1
unnamed: Q52.3, R180.1
unnamed: Q52.1, R192.1
unnamed: Q53.3, R189.1
unnamed: Q53.1, R193.1
unnamed: Q54.3, R190.1
unnamed: Q54.1, R194.1
unnamed: J31.SHLD1, J31.SHLD2, J31.SHLD3, J31.SHLD4, J31.SHLD5, J31.SHLD6, J31.SHLD7, J31.SHLD8, JP28.2
unnamed: Q55.3, Q56.1, R196.2
unnamed: Q55.2, Q55.5, Q55.6, R195.2
unnamed: D67.C, R207.2
unnamed: D66.C, R208.2
unnamed: C87.2, U24.1, Y8.P$2
unnamed: C88.1, U24.2, Y8.P$1
unnamed: D64.C, R203.2
unnamed: D65.C, R204.2
unnamed: JP30.1, R213.2
unnamed: JP31.1, R215.2
unnamed: D69.C, R216.2
unnamed: D70.C, R217.2
unnamed: D71.C, R218.2
unnamed: Q59.3, R216.1
unnamed: Q59.1, R219.1
unnamed: Q60.3, R208.1
unnamed: Q60.1, R220.1
unnamed: Q61.3, R217.1
unnamed: Q61.1, R221.1
unnamed: Q62.3, R218.1
unnamed: Q62.1, R222.1
unnamed: J36.SHLD1, J36.SHLD2, J36.SHLD3, J36.SHLD4, J36.SHLD5, J36.SHLD6, J36.SHLD7, J36.SHLD8, JP32.2
unnamed: Q63.3, Q64.1, R224.2
unnamed: Q63.2, Q63.5, Q63.6, R223.2
unnamed: D76.C, R235.2
unnamed: D75.C, R236.2
unnamed: C98.2, U27.1, Y9.P$2
unnamed: C99.1, U27.2, Y9.P$1
unnamed: D73.C, R231.2
unnamed: D74.C, R232.2
unnamed: JP34.1, R241.2
unnamed: JP35.1, R243.2
unnamed: D78.C, R244.2
unnamed: D79.C, R245.2
unnamed: D80.C, R246.2
unnamed: Q67.3, R244.1
unnamed: Q67.1, R247.1
unnamed: Q68.3, R236.1
unnamed: Q68.1, R248.1
unnamed: Q69.3, R245.1
unnamed: Q69.1, R249.1
unnamed: Q70.3, R246.1
unnamed: Q70.1, R250.1
unnamed: J41.SHLD1, J41.SHLD2, J41.SHLD3, J41.SHLD4, J41.SHLD5, J41.SHLD6, J41.SHLD7, J41.SHLD8, JP36.2
unnamed: Q71.3, Q72.1, R252.2
unnamed: Q71.2, Q71.5, Q71.6, R251.2
unnamed: D85.C, R263.2
unnamed: D84.C, R264.2
unnamed: C109.2, U30.1, Y10.P$2
unnamed: C110.1, U30.2, Y10.P$1
unnamed: D82.C, R259.2
unnamed: D83.C, R260.2
unnamed: JP38.1, R269.2
unnamed: JP39.1, R271.2
unnamed: D87.C, R272.2
unnamed: D88.C, R273.2
unnamed: D89.C, R274.2
unnamed: Q75.3, R272.1
unnamed: Q75.1, R275.1
unnamed: Q76.3, R264.1
unnamed: Q76.1, R276.1
unnamed: Q77.3, R273.1
unnamed: Q77.1, R277.1
unnamed: Q78.3, R274.1
unnamed: Q78.1, R278.1
unnamed: J46.SHLD1, J46.SHLD2, J46.SHLD3, J46.SHLD4, J46.SHLD5, J46.SHLD6, J46.SHLD7, J46.SHLD8, JP40.2
unnamed: Q79.3, Q80.1, R280.2
unnamed: Q79.2, Q79.5, Q79.6, R279.2
RX-I_HV: J5.2, Q2.3, R13.1, TP7.1
RX-I_HV1: J10.2, Q9.3, R45.1, TP20.1
RX-I_HV2: J15.2, Q17.3, R73.1, TP33.1
RX-I_HV3: J20.2, Q25.3, R101.1, TP46.1
RX-I_HV4: J25.2, Q33.3, R129.1, TP59.1
RX-I_HV5: J30.2, Q41.3, R157.1, TP72.1
RX-I_HV6: J35.2, Q49.3, R185.1, TP85.1
RX-I_HV7: J40.2, Q57.3, R213.1, TP98.1
RX-I_HV8: J45.2, Q65.3, R241.1, TP111.1
RX-I_HV9: J50.2, Q73.3, R269.1, TP124.1
RX-I_LV: Q2.2, R11.1, U2.16
RX-I_LV1: Q9.2, R44.1, U6.16
RX-I_LV2: Q17.2, R72.1, U9.16
RX-I_LV3: Q25.2, R100.1, U12.16
RX-I_LV4: Q33.2, R128.1, U15.16
RX-I_LV5: Q41.2, R156.1, U18.16
RX-I_LV6: Q49.2, R184.1, U21.16
RX-I_LV7: Q57.2, R212.1, U24.16
RX-I_LV8: Q65.2, R240.1, U27.16
RX-I_LV9: Q73.2, R268.1, U30.16
SAMD_!RESET!: J4.10, R10.1, S3.1, S3.2, TP5.1, U2.40
SAMD_!RESET!1: J8.10, R41.1, S2.1, S2.2, TP18.1, U6.40
SAMD_!RESET!2: J13.10, R69.1, S5.1, S5.2, TP31.1, U9.40
SAMD_!RESET!3: J18.10, R97.1, S7.1, S7.2, TP44.1, U12.40
SAMD_!RESET!4: J23.10, R125.1, S9.1, S9.2, TP57.1, U15.40
SAMD_!RESET!5: J28.10, R153.1, S11.1, S11.2, TP70.1, U18.40
SAMD_!RESET!6: J33.10, R181.1, S13.1, S13.2, TP83.1, U21.40
SAMD_!RESET!7: J38.10, R209.1, S15.1, S15.2, TP96.1, U24.40
SAMD_!RESET!8: J43.10, R237.1, S17.1, S17.2, TP109.1, U27.40
SAMD_!RESET!9: J48.10, R265.1, S19.1, S19.2, TP122.1, U30.40
SCL_PU1: JP9.1, R3.2
SCL_PU2: JP4.1, R42.2
SCL_PU3: JP8.1, R70.2
SCL_PU4: JP13.1, R98.2
SCL_PU5: JP17.1, R126.2
SCL_PU6: JP21.1, R154.2
SCL_PU7: JP25.1, R182.2
SCL_PU8: JP29.1, R210.2
SCL_PU9: JP33.1, R238.2
SCL_PU10: JP37.1, R266.2
SDA_PU1: JP9.3, R6.2
SDA_PU2: JP4.3, R43.2
SDA_PU3: JP8.3, R71.2
SDA_PU4: JP13.3, R99.2
SDA_PU5: JP17.3, R127.2
SDA_PU6: JP21.3, R155.2
SDA_PU7: JP25.3, R183.2
SDA_PU8: JP29.3, R211.2
SDA_PU9: JP33.3, R239.2
SDA_PU10: JP37.3, R267.2
SWCLK: J4.4, TP4.1, U2.45
SWCLK1: J8.4, TP17.1, U6.45
SWCLK2: J13.4, TP30.1, U9.45
SWCLK3: J18.4, TP43.1, U12.45
SWCLK4: J23.4, TP56.1, U15.45
SWCLK5: J28.4, TP69.1, U18.45
SWCLK6: J33.4, TP82.1, U21.45
SWCLK7: J38.4, TP95.1, U24.45
SWCLK8: J43.4, TP108.1, U27.45
SWCLK9: J48.4, TP121.1, U30.45
SWDIO: J4.2, TP3.1, U2.46
SWDIO1: J8.2, TP16.1, U6.46
SWDIO2: J13.2, TP29.1, U9.46
SWDIO3: J18.2, TP42.1, U12.46
SWDIO4: J23.2, TP55.1, U15.46
SWDIO5: J28.2, TP68.1, U18.46
SWDIO6: J33.2, TP81.1, U21.46
SWDIO7: J38.2, TP94.1, U24.46
SWDIO8: J43.2, TP107.1, U27.46
SWDIO9: J48.2, TP120.1, U30.46
TX-O: J5.3, TP8.1, U2.15
TX-O1: J10.3, TP21.1, U6.15
TX-O2: J15.3, TP34.1, U9.15
TX-O3: J20.3, TP47.1, U12.15
TX-O4: J25.3, TP60.1, U15.15
TX-O5: J30.3, TP73.1, U18.15
TX-O6: J35.3, TP86.1, U21.15
TX-O7: J40.3, TP99.1, U24.15
TX-O8: J45.3, TP112.1, U27.15
TX-O9: J50.3, TP125.1, U30.15
VCC_CABLE: J5.1, Q7.1, Q8.3
VCC_CABLE1: J10.1, Q15.1, Q16.3
VCC_CABLE2: J15.1, Q23.1, Q24.3
VCC_CABLE3: J20.1, Q31.1, Q32.3
VCC_CABLE4: J25.1, Q39.1, Q40.3
VCC_CABLE5: J30.1, Q47.1, Q48.3
VCC_CABLE6: J35.1, Q55.1, Q56.3
VCC_CABLE7: J40.1, Q63.1, Q64.3
VCC_CABLE8: J45.1, Q71.1, Q72.3
VCC_CABLE9: J50.1, Q79.1, Q80.3
VDDCORE: C13.1, U2.43
VDDCORE1: C17.1, U6.43
VDDCORE2: C29.1, U9.43
VDDCORE3: C40.1, U12.43
VDDCORE4: C51.1, U15.43
VDDCORE5: C62.1, U18.43
VDDCORE6: C73.1, U21.43
VDDCORE7: C84.1, U24.43
VDDCORE8: C95.1, U27.43
VDDCORE9: C106.1, U30.43
VUSB: F1.1, J3.VBUS1, J3.VBUS2
VUSB1: F2.1, J2.VBUS1, J2.VBUS2
VUSB2: F3.1, J11.VBUS1, J11.VBUS2
VUSB3: F4.1, J16.VBUS1, J16.VBUS2
VUSB4: F5.1, J21.VBUS1, J21.VBUS2
VUSB5: F6.1, J26.VBUS1, J26.VBUS2
VUSB6: F7.1, J31.VBUS1, J31.VBUS2
VUSB7: F8.1, J36.VBUS1, J36.VBUS2
VUSB8: F9.1, J41.VBUS1, J41.VBUS2
VUSB9: F10.1, J46.VBUS1, J46.VBUS2
V_USB: D9.A, F1.2
V_USB1: D18.A, F2.2
V_USB2: D27.A, F3.2
V_USB3: D36.A, F4.2
V_USB4: D45.A, F5.2
V_USB5: D54.A, F6.2
V_USB6: D63.A, F7.2
V_USB7: D72.A, F8.2
V_USB8: D81.A, F9.2
V_USB9: D90.A, F10.2
